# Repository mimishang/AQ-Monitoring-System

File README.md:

# AQ-Monitoring-System
Documentation and version control of Mimi Low Cost Air Quality Monitoring System

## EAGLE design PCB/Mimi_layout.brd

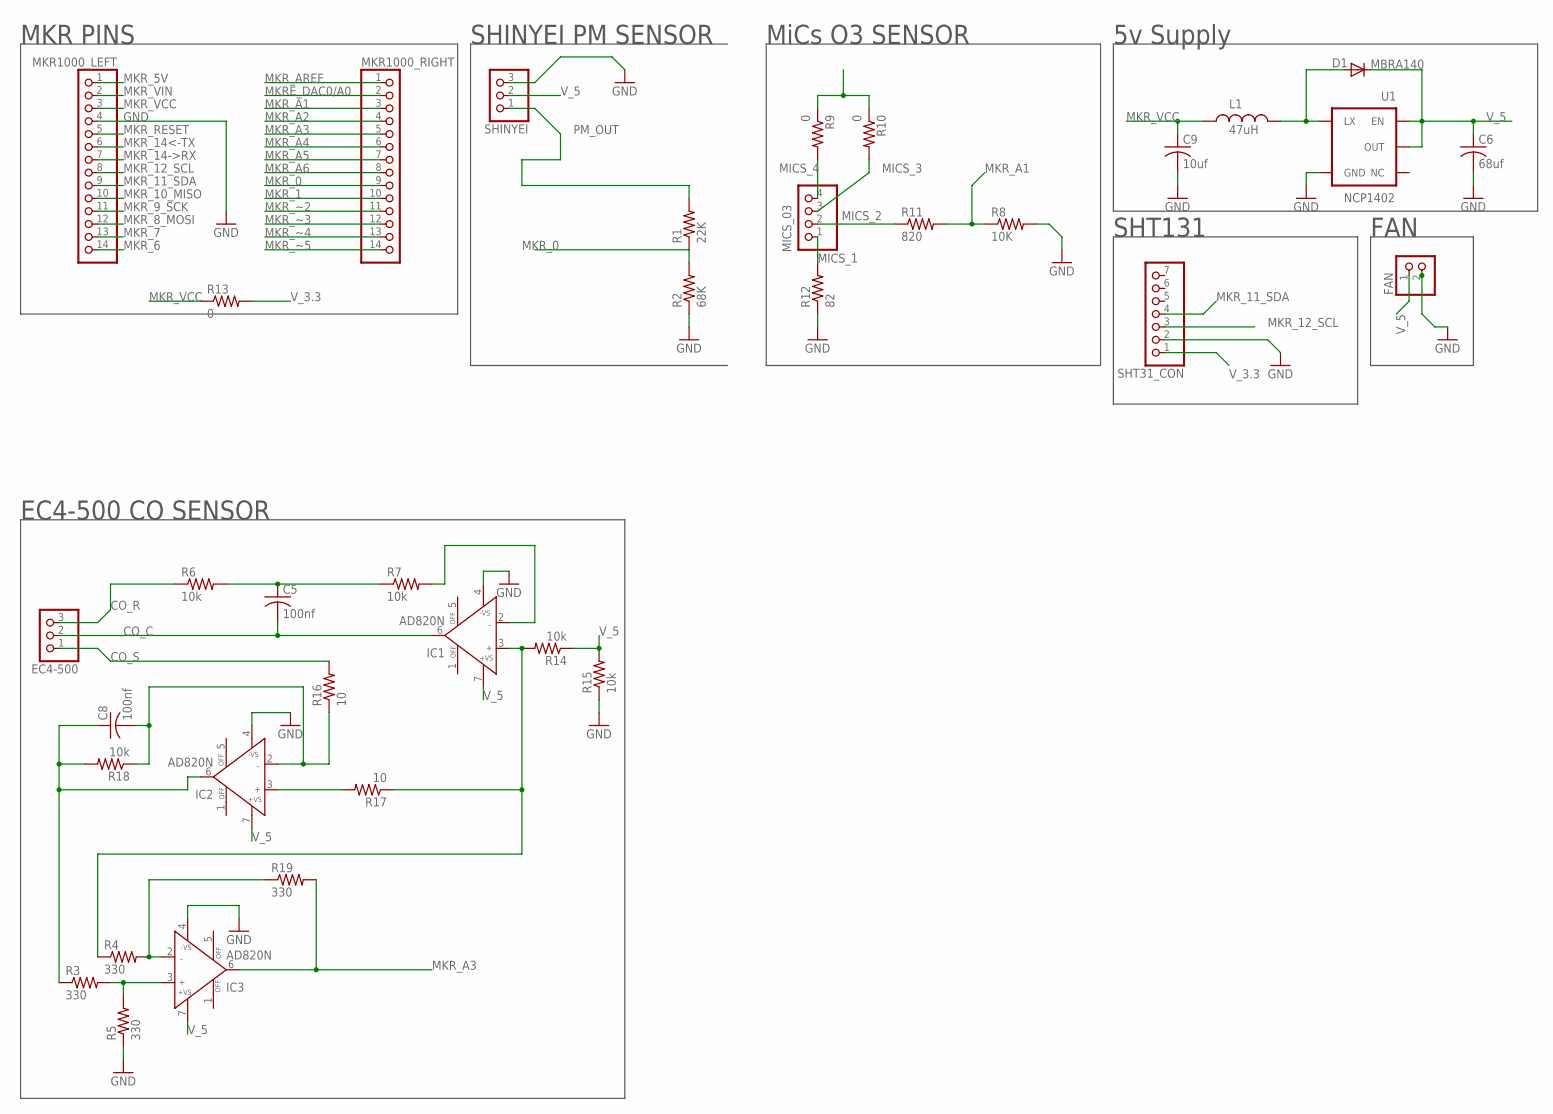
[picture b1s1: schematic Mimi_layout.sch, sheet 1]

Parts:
C5, C8: 100nf; C0805
C6: 68uf; C0805
C9: 10uf; C0805
D1: MBRA140; SMA-DIODE
EC4-500: PINHD-1X3; 1X03
FAN: PINHD-1X2; 1X02
IC1, IC2, IC3: AD820N; DIL08
L1: 47uH; CR54
MICS_03: PINHD-1X4; 1X04
MKR1000_LEFT, MKR1000_RIGHT: PINHD-1X14; 1X14
R1: 22K; R0805
R2: 68K; R0805
R3, R4, R5, R19: 330; R0805
R6, R7, R14, R15, R18: 10k; R0805
R8: 10K; R0805
R9, R10, R13: 0; R0805
R11: 820; R0805
R12: 82; R0805
R16, R17: 10; R0805
SHINYEI: PINHD-1X3; 1X03
SHT31_CON: PINHD-1X7; 1X07
U1: NCP1402; SOT23-5

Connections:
CO_C: C5.2, EC4-500.2, IC1.6 (OUT)
CO_R: EC4-500.3, R6.1
CO_S: EC4-500.1, R16.2
GND: C6.2, C9.2, FAN.2, IC1.4 (-VS), IC2.4 (-VS), IC3.4 (-VS), MKR1000_LEFT.4, R2.1, R5.1, R8.2, R12.1, R15.1, SHINYEI.3, SHT31_CON.2, U1.4 (GND)
MICS_1: MICS_03.1, R12.2
MICS_2: MICS_03.2, R11.1
MICS_3: MICS_03.3, R10.2
MICS_4: MICS_03.4, R9.2
MKRE_DAC0/A0: MKR1000_RIGHT.2
MKR_0: MKR1000_RIGHT.9, R1.1, R2.2
MKR_1: MKR1000_RIGHT.10
MKR_5V: MKR1000_LEFT.1
MKR_6: MKR1000_LEFT.14
MKR_7: MKR1000_LEFT.13
MKR_8_MOSI: MKR1000_LEFT.12
MKR_9_SCK: MKR1000_LEFT.11
MKR_10_MISO: MKR1000_LEFT.10
MKR_11_SDA: MKR1000_LEFT.9, SHT31_CON.4
MKR_12_SCL: MKR1000_LEFT.8, SHT31_CON.3
MKR_14->RX: MKR1000_LEFT.7
MKR_14<-TX: MKR1000_LEFT.6
MKR_A1: MKR1000_RIGHT.3, R8.1, R11.2
MKR_A2: MKR1000_RIGHT.4
MKR_A3: IC3.6 (OUT), MKR1000_RIGHT.5, R19.2
MKR_A4: MKR1000_RIGHT.6
MKR_A5: MKR1000_RIGHT.7
MKR_A6: MKR1000_RIGHT.8
MKR_AREF: MKR1000_RIGHT.1
MKR_RESET: MKR1000_LEFT.5
MKR_VCC: C9.1, L1.P$1 (1), MKR1000_LEFT.3, R13.1
MKR_VIN: MKR1000_LEFT.2
MKR_~2: MKR1000_RIGHT.11
MKR_~3: MKR1000_RIGHT.12
MKR_~4: MKR1000_RIGHT.13
MKR_~5: MKR1000_RIGHT.14
unnamed: D1.A, L1.P$2 (2), U1.5 (LX)
unnamed: C5.1, R6.2, R7.1
unnamed: IC1.3 (IN+), R4.1, R14.2, R17.1
unnamed: IC1.2 (IN-), R7.2
unnamed: IC2.3 (IN+), R17.2
unnamed: C8.2, IC2.2 (IN-), R16.1, R18.1
unnamed: C8.1, IC2.6 (OUT), R3.1, R18.2
unnamed: IC3.3 (IN+), R3.2, R5.2
unnamed: IC3.2 (IN-), R4.2, R19.1
PM_OUT: R1.2, SHINYEI.1
V_3.3: R13.2, SHT31_CON.1
V_5: C6.1, D1.C, FAN.1, IC1.7 (+VS), IC2.7 (+VS), IC3.7 (+VS), R9.1, R10.1, R14.1, R15.2, SHINYEI.2, U1.1 (EN), U1.2 (OUT)

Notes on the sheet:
EC4-500 CO SENSOR
MiCs O3 SENSOR
SHINYEI PM SENSOR
MKR PINS
SHT131
FAN
5v Supply

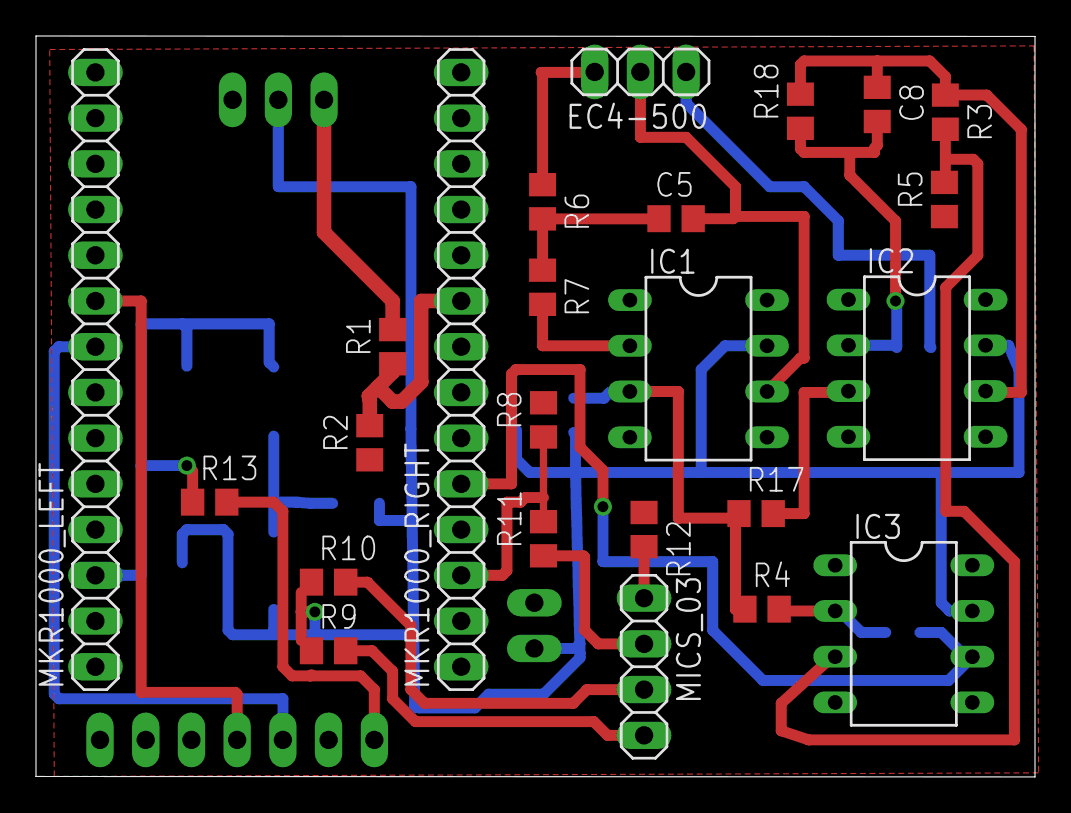
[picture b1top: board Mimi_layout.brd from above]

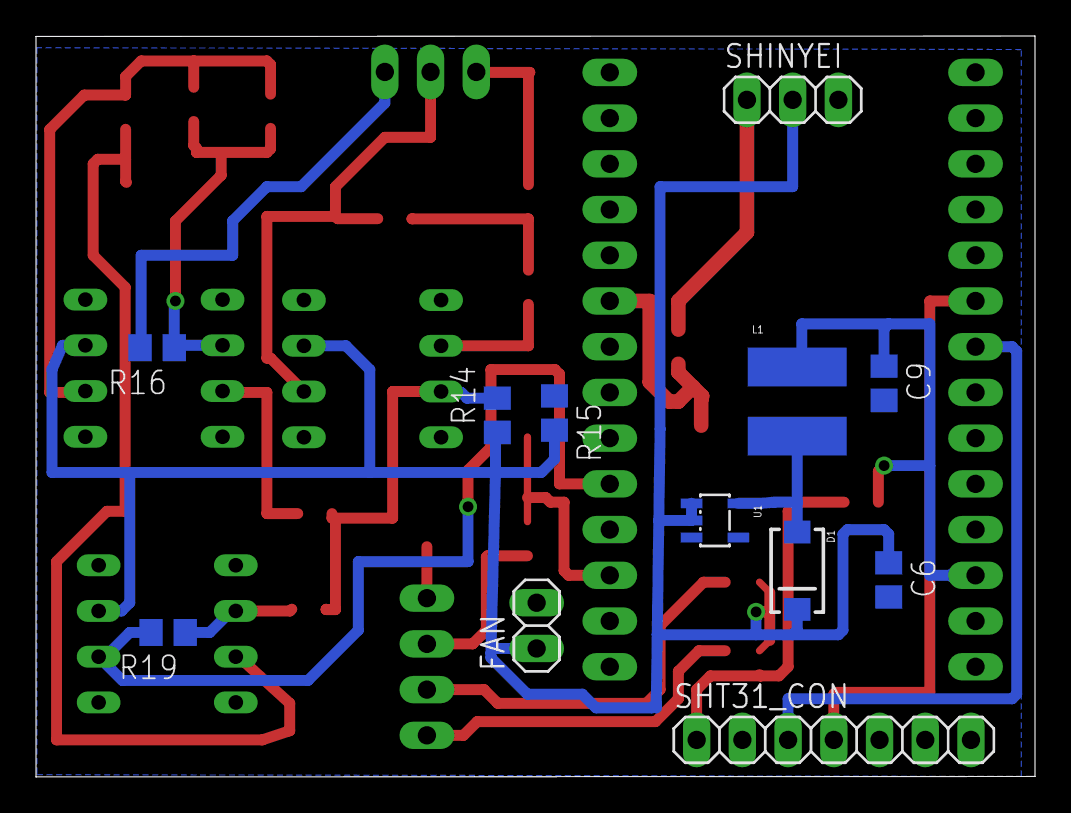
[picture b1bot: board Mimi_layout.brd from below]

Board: 2 copper layers, 55.5 x 41.2 mm, 36 parts (12 on the bottom side), 26 nets.

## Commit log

2017-04-19 board V1
2017-04-19 Layout V2
2017-04-19 Board V3
    Version 3 of the schematic and board. might be able to shrink a little more but everything is pretty tight as is.
    Also added EPL LPKF CAM/DRU files for making GBRs for manufacturing and ensuring the layout does not violate machine tolerances
2017-04-19 screenshots
    Thought some screengrabs of the schematic and layout would be nice
2017-04-19 Create Code
2017-04-19 got rid of bad file
2017-04-19 dummy file for prettier folder names
2017-04-19 ozone sensor test program
2017-04-19 PM sensor test program
2017-04-19 previously uploaded the wrong code
2017-04-19 added MKR pinout
2017-04-19 test program for SHT31-d
2017-04-19 Add files via upload
    This is the actual code that will be run on the MKR that is to be inserted into the PCBs.
    it currently has a few bugs and variable names aren't great since its basically an extended version of a pushingbox API test that was done to make sure data could be sent to a google sheets document.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
2017-04-19 fixed serial print info
    the names are right at least, still need to make the formatting better
2017-04-19 PPM sensor datasheet
2017-04-19 Flow Sensor Datasheet
2017-04-19 CO sensor schematic
2017-04-19 CO sensor Datasheet
2017-04-19 more CO sensor schematic information
2017-04-19 clearer flow sensor schematic
    it was hard to tell what pins went where from the datasheet schematic, this makes things much clearer
2017-04-19 more FS2 information
    manual for a whole PCB built around the FS2 flow sensor
2017-04-19 Better pinout documentation
    added a little blurb near the top to say which pins are connected to what.
2017-04-19 many small fixes
    Can connect to PSU unsecured wifi now!
    better output formatting.
    for some reason the program hangs when it tries to access the SHT31.
    data received from PM sensor seems questionable (outputs 0 always)
2017-04-21 compression & schematic fixes
    board dimensions shrunk to 2.18 * 1.62. will try to compress further but from this point on there will be diminishing returns on time spent vs resulting compression.
    also fixed a few warnings in schematic capture mode. there are still some but none are serious problems.
2017-04-21 new images to reflect compression
2017-04-21 small fixes
    removed a couple more DRC errors
2017-04-21 Partlist
    has a list of all the parts in the schematic and layout. its worth noting that the opamps being used are different since eagle had a library with a component of the same dimensions. I'll make a sprea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
2017-04-26 better names, first in a series of updates
    after a series of failures i have began to take a more systematic approach to fixing the naming of the stuff that allows the MKR to talk to pushingbox and google spreadsheets. step 1 was updating the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
2017-05-05 capacitor fix
    removed oversize capacitors (1206) and replaced with 0805s
2017-05-24 small fixes
    switched a couple values from int to float to allow higher resolution readings, changed port configuration to an input
2017-05-24 replaced components, rerouted
    a few components were removed and resistances changed in accordance with observed device behavior

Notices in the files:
parts and their libraries:
SparkFun-Aesthetics: Licensing: Creative Commons ShareAlike 4.0 International - https://creativecommons.org/licenses/by-sa/4.0
